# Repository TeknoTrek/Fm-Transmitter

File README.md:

# FM Transmitter (88 MHz – 108 MHz)

This repository contains the KiCad project files for an FM Transmitter circuit operating in the 88 MHz – 108 MHz range. The design includes both the circuit schematic and the PCB layout, with a 3D model of the assembled board.

## Project Overview

This FM transmitter is designed to broadcast audio signals using a microphone input. It covers the standard FM radio frequency range and is powered by a 9V battery. The circuit is based on a single transistor (BC548) and includes adjustable frequency tuning through a variable capacitor (C3).

### Features:
- Frequency Range: 88 MHz – 108 MHz
- Microphone input for real-time audio transmission
- LED power indicator
- Compact PCB design
- Easy to assemble

## Watch the Build Process

You can watch the full build process of this FM transmitter on my YouTube channel [**Teknotrek**](https://www.youtube.com/@TeknoTrek). Click the link below to see how the circuit is assembled, soldered, and tested:

[Watch on YouTube](https://youtu.be/xPGkkRPhaV4)

## Circuit Schematic

The circuit consists of the following key components:
- **Q1 (BC548)**: The main transistor used for signal amplification and modulation.
- **C3 (0-30 pF)**: A variable capacitor for tuning the frequency.
- **L1 (Coil)**: Works with C3 to set the oscillation frequency.
- **Microphone**: Captures the audio to be transmitted.
- **Antenna**: Transmits the modulated FM signal.

## PCB Layout

The PCB layout is designed to be compact, with clear labels for easy assembly. The board supports through-hole components for easier soldering.

## 3D Model

A 3D model of the assembled PCB is included to give you a better idea of how the final product will look.

## Getting Started

1. Clone the repository:
   ```bash
   git clone https://github.com/TeknoTrek/fm-transmitter.git
   ```

2. Open the project in KiCad and review the schematic and PCB layout.

3. Assemble the components as per the schematic, solder them to the PCB, and tune the frequency using C3.

4. Attach a suitable antenna and power the transmitter using a 9V battery.

---

Let me know if you'd like to adjust any part of it!

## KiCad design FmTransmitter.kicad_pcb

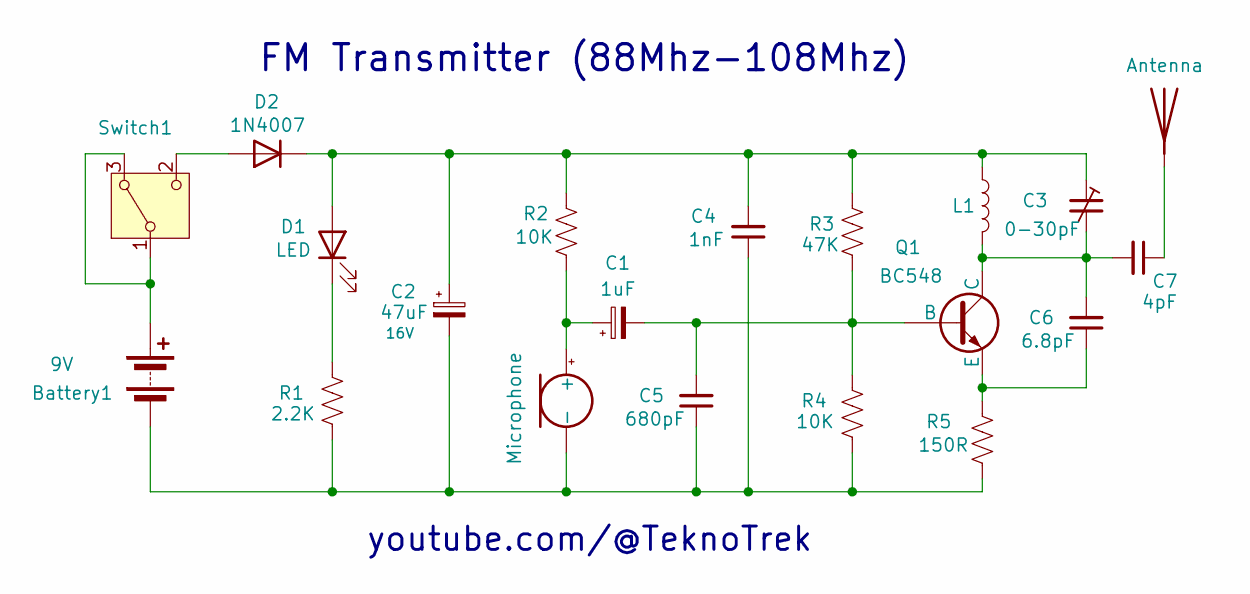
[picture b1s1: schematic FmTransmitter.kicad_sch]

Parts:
AE1: Antenna; PinHeader_1x01_P2.54mm_Vertical
Battery1: 9V; PinHeader_1x02_P2.54mm_Vertical
C1: 1uF; CP_Radial_D5.0mm_P2.50mm
C2: 47uF; CP_Radial_D5.0mm_P2.50mm
C3: 0-30pF; C_Disc_D6.0mm_W4.4mm_P6.00mm_x
C4: 1nF; C_Disc_D5.0mm_W2.5mm_P5.00mm
C5: 680pF; C_Disc_D3.0mm_W1.6mm_P2.50mm
C6: 6.8pF; C_Disc_D3.0mm_W1.6mm_P2.50mm
C7: 4pF; C_Disc_D3.0mm_W1.6mm_P2.50mm
D1: LED; LED_D3.0mm
D2: 1N4007; D_DO-41_SOD81_P10.16mm_Horizontal
L1: L; L_Axial_L7.0mm_D3.3mm_P6.00mm_Horizontal_Fastron
MK1: Microphone; MagneticBuzzer_Kingstate_KCG0601
Q1: BC548; TO-92_Wide
R1: 2.2K; R_Axial_DIN0207_L6.3mm_D2.5mm_P10.16mm_Horizontal
R2, R4: 10K; R_Axial_DIN0207_L6.3mm_D2.5mm_P10.16mm_Horizontal
R3: 47K; R_Axial_DIN0207_L6.3mm_D2.5mm_P10.16mm_Horizontal
R5: 150R; R_Axial_DIN0207_L6.3mm_D2.5mm_P10.16mm_Horizontal
Switch1: SW; SW_Slide-03_Wuerth-WS-SLTV_10x2.5x6.4_P2.54mm

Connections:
GND: Battery1.2 (-), C2.2, C4.1, C5.1, MK1.1 (-), R1.2, R4.2, R5.2
unnamed: AE1.1 (A), C7.1
unnamed: Battery1.1 (+), Switch1.1 (B), Switch1.3 (A)
unnamed: C2.1, C3.1, C4.2, D1.2 (A), D2.1 (K), L1.1, R2.1, R3.1
unnamed: D1.1 (K), R1.1
unnamed: D2.2 (A), Switch1.2 (C)
unnamed: C1.1, MK1.2 (+), R2.2
unnamed: C1.2, C5.2, Q1.2 (B), R3.2, R4.1
unnamed: C3.2, C6.2, C7.2, L1.2, Q1.1 (C)
unnamed: C6.1, Q1.3 (E), R5.1

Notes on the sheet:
FM Transmitter (88Mhz-108Mhz)
youtube.com/@TeknoTrek

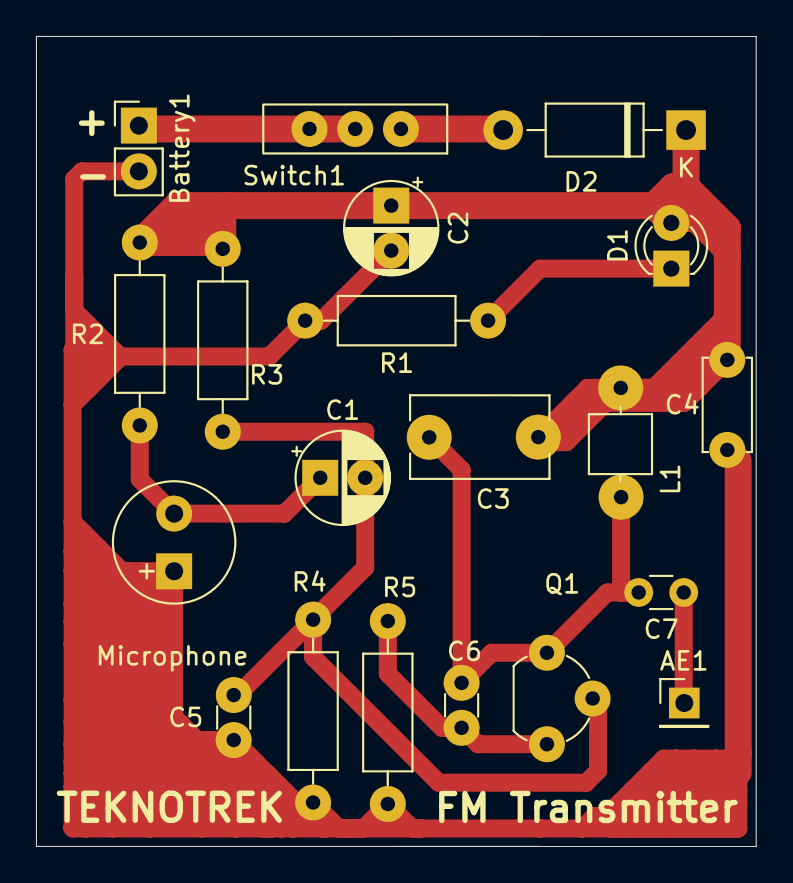
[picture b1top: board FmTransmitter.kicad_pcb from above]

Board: 2 copper layers, 40.0 x 45.0 mm, 20 parts (0 on the bottom side), 10 nets.
